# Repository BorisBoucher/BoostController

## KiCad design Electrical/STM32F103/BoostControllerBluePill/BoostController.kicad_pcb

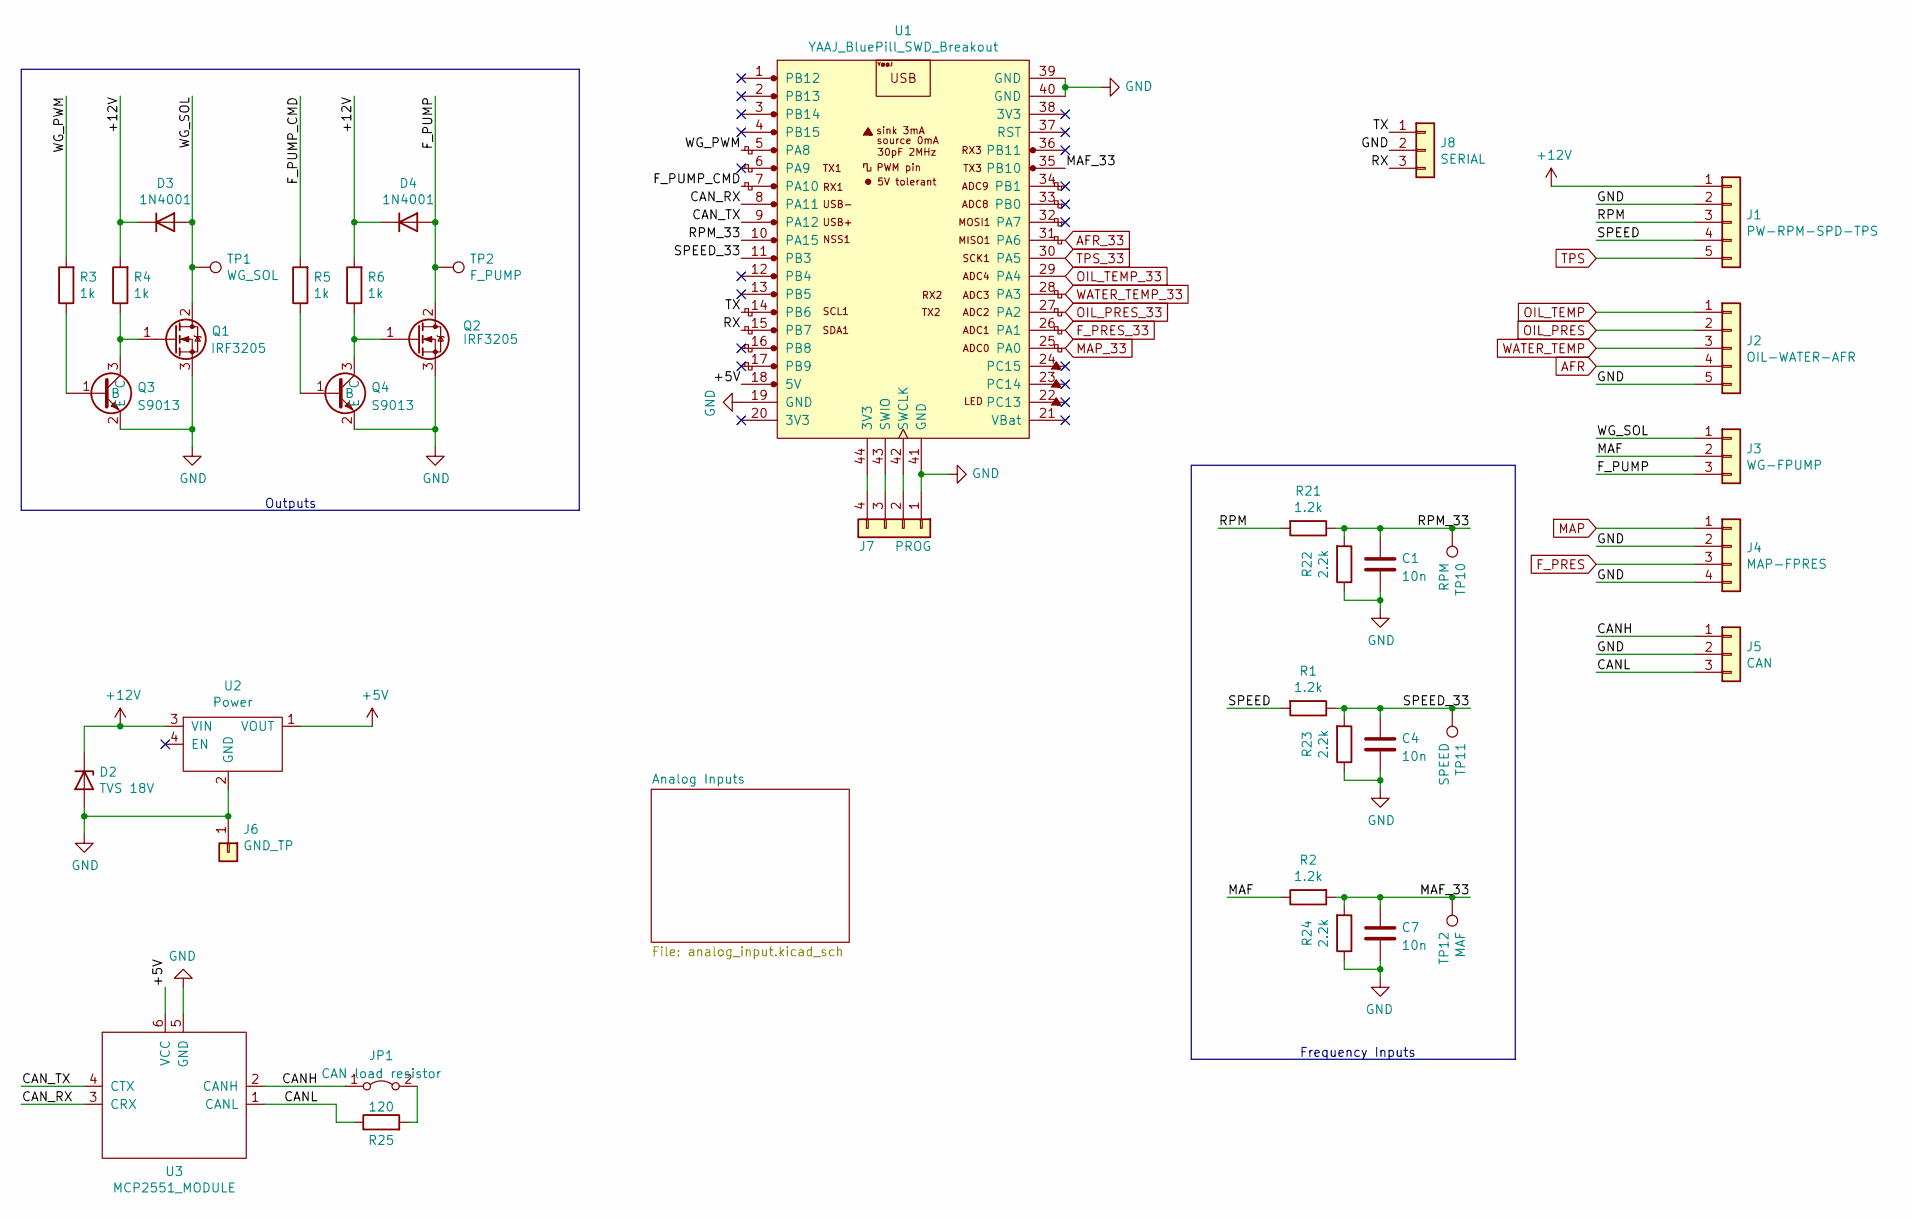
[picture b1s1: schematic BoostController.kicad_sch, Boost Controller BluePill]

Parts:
C1, C4, C7: 10n; C_0603_1608Metric_Pad1.08x0.95mm_HandSolder
D2: TVS 18V; D_DO-41_SOD81_P5.08mm_Vertical_AnodeUp
D3, D4: 1N4001; D_DO-41_SOD81_P2.54mm_Vertical_AnodeUp
J1: PW-RPM-SPD-TPS; JST_XH_S5B-XH-A-1_1x05_P2.50mm_Horizontal
J2: OIL-WATER-AFR; JST_XH_S5B-XH-A-1_1x05_P2.50mm_Horizontal
J3: WG-FPUMP; JST_XH_S3B-XH-A-1_1x03_P2.50mm_Horizontal
J4: MAP-FPRES; JST_XH_S4B-XH-A-1_1x04_P2.50mm_Horizontal
J5: CAN; JST_XH_S3B-XH-A-1_1x03_P2.50mm_Horizontal
J6: GND_TP; Pin_Header_Straight_1x01_Pitch2.54mm
J7: PROG; PinHeader_1x04_P2.54mm_Vertical
J8: SERIAL; PinHeader_1x03_P2.54mm_Vertical
JP1: CAN load resistor; PinHeader_1x02_P2.54mm_Vertical
Q1, Q2: IRF3205; TO-220-3_Vertical
Q3, Q4: S9013; SOT-23
R1, R2, R21: 1.2k; R_1206_3216Metric_Pad1.30x1.75mm_HandSolder
R3, R4, R5, R6: 1k; R_1206_3216Metric_Pad1.30x1.75mm_HandSolder
R22, R23, R24: 2.2k; R_1206_3216Metric_Pad1.30x1.75mm_HandSolder
R25: 120; R_1206_3216Metric_Pad1.30x1.75mm_HandSolder
TP1: WG_SOL; Measurement_Point_Round-SMD-Pad_Big
TP2: F_PUMP; Measurement_Point_Round-SMD-Pad_Big
TP10: RPM; TestPoint_Pad_D3.0mm
TP11: SPEED; TestPoint_Pad_D3.0mm
TP12: MAF; TestPoint_Pad_D3.0mm
U1: YAAJ_BluePill_SWD_Breakout; YAAJ_BluePill_SWD_1
U2: Power; MICRO-BUCK-POWER-MODULE_FLAT
U3: MCP2551_MODULE

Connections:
+5V: U1.18 (5V), U2.1 (VOUT), U3.6 (VCC); also elsewhere on the board
+12V: D2.1 (K), D3.1 (K), D4.1 (K), J1.1, R4.2, R6.2, U2.3 (VIN)
/CANH: J5.1, JP1.1 (A), U3.2 (CANH)
/CANL: J5.3, R25.1, U3.1 (CANL)
/CAN_RX: U1.8 (PA11), U3.3 (CRX)
/CAN_TX: U1.9 (PA12), U3.4 (CTX)
/F_PUMP: D4.2 (A), J3.3, Q2.2 (D), TP2.1
/F_PUMP_CMD: R5.2, U1.7 (PA10)
/MAF: J3.2, R2.1
/MAF_33: C7.1, R2.2, R24.2, TP12.1, U1.35 (PB10)
/RPM: J1.3, R21.2
/RPM_33: C1.1, R21.1, R22.2, TP10.1, U1.10 (PA15)
/RX: J8.3, U1.15 (PB7)
/SPEED: J1.4, R1.2
/SPEED_33: C4.1, R1.1, R23.2, TP11.1, U1.11 (PB3)
/TX: J8.1, U1.14 (PB6)
/WG_PWM: R3.2, U1.5 (PA8)
/WG_SOL: D3.2 (A), J3.1, Q1.2 (D), TP1.1
AFR: J2.4; also elsewhere on the board
AFR_33: U1.31 (PA6); also elsewhere on the board
F_PRES: J4.3; also elsewhere on the board
F_PRES_33: U1.26 (PA1); also elsewhere on the board
GND: C1.2, C4.2, C7.2, D2.2 (A), J1.2, J2.5, J4.2, J4.4, J5.2, J6.1, J7.1, J8.2, Q1.3 (S), Q2.3 (S), Q3.2 (E), Q4.2 (E), R22.1, R23.1, R24.1, U1.19 (GND), U1.39 (GND), U1.40 (GND), U1.41 (GND), U2.2 (GND), U3.5 (GND); also elsewhere on the board
MAP: J4.1; also elsewhere on the board
MAP_33: U1.25 (PA0); also elsewhere on the board
unnamed: J7.2, U1.42 (SWCLK)
unnamed: J7.3, U1.43 (SWIO)
unnamed: J7.4, U1.44 (3V3)
unnamed: JP1.2 (B), R25.2
unnamed: Q1.1 (G), Q3.3 (C), R4.1
unnamed: Q2.1 (G), Q4.3 (C), R6.1
unnamed: Q3.1 (B), R3.1
unnamed: Q4.1 (B), R5.1
OIL_PRES: J2.2; also elsewhere on the board
OIL_PRES_33: U1.27 (PA2); also elsewhere on the board
OIL_TEMP: J2.1; also elsewhere on the board
OIL_TEMP_33: U1.29 (PA4); also elsewhere on the board
TPS: J1.5; also elsewhere on the board
TPS_33: U1.30 (PA5); also elsewhere on the board
WATER_TEMP: J2.3; also elsewhere on the board
WATER_TEMP_33: U1.28 (PA3); also elsewhere on the board

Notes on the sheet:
Frequency Inputs
Outputs

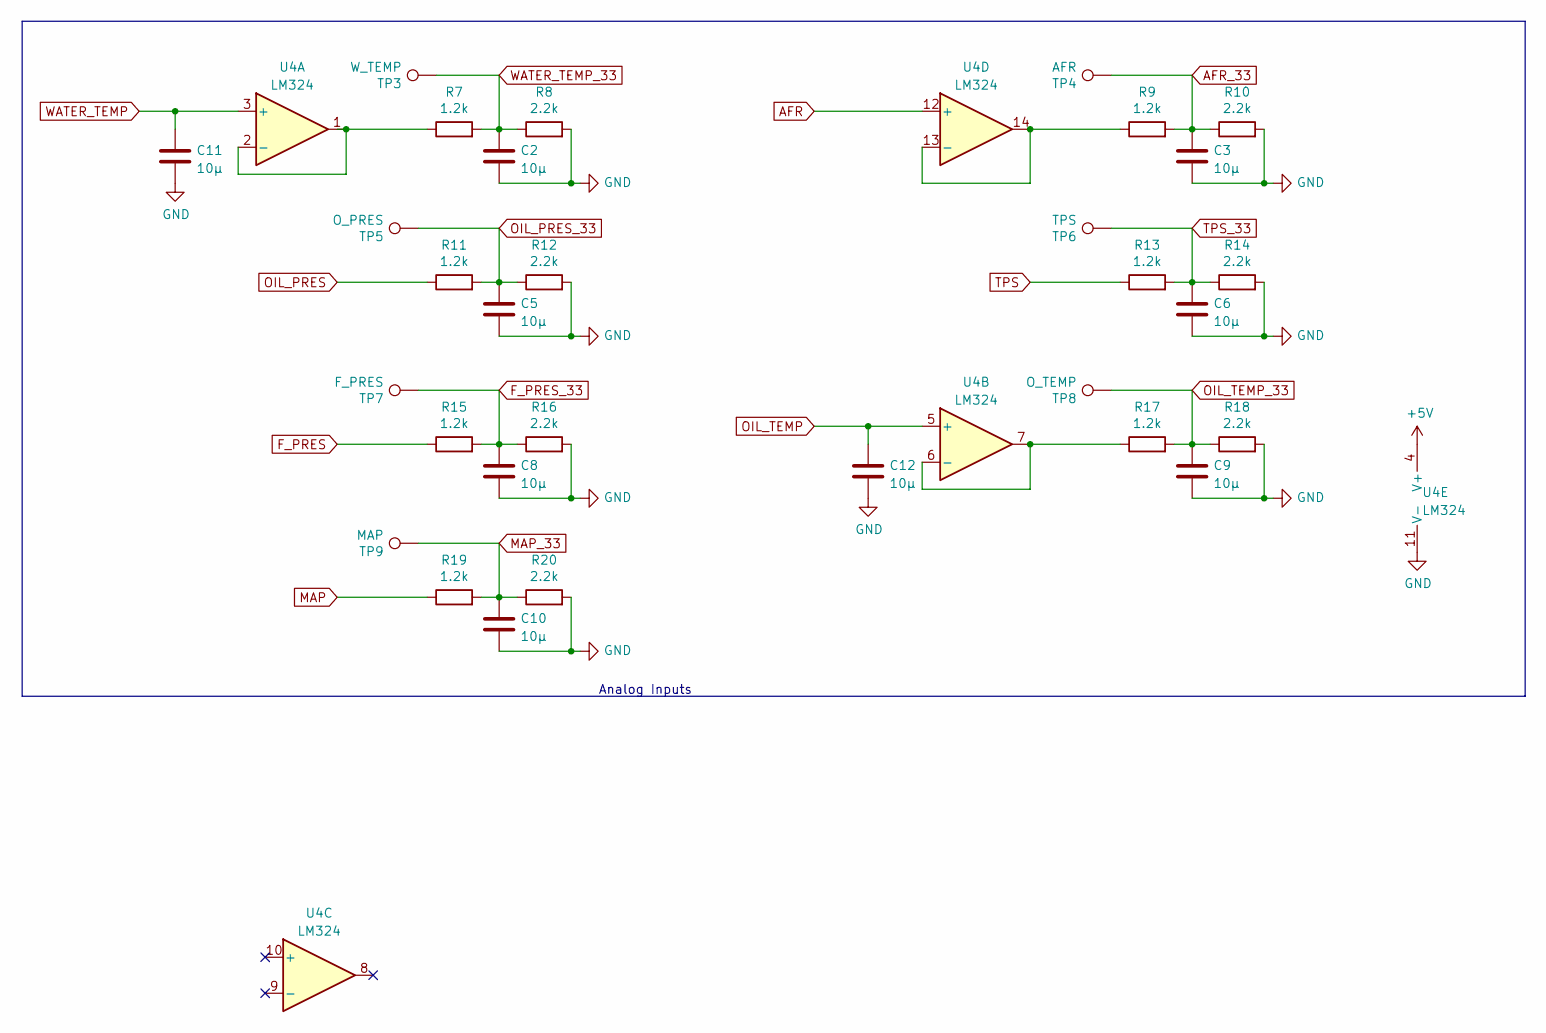
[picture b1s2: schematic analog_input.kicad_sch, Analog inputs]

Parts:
C2, C3, C5, C6, C8, C9, C10, C11, C12: 10µ; C_0603_1608Metric_Pad1.08x0.95mm_HandSolder
R7, R9, R11, R13, R15, R17, R19: 1.2k; R_1206_3216Metric_Pad1.30x1.75mm_HandSolder
R8, R10, R12, R14, R16, R18, R20: 2.2k; R_1206_3216Metric_Pad1.30x1.75mm_HandSolder
TP3: W_TEMP; Measurement_Point_Round-SMD-Pad_Big
TP4: AFR; Measurement_Point_Round-SMD-Pad_Big
TP5: O_PRES; Measurement_Point_Round-SMD-Pad_Big
TP6: TPS; Measurement_Point_Round-SMD-Pad_Big
TP7: F_PRES; Measurement_Point_Round-SMD-Pad_Big
TP8: O_TEMP; Measurement_Point_Round-SMD-Pad_Big
TP9: MAP; Measurement_Point_Round-SMD-Pad_Big
U4: LM324

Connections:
+5V: U4.4 (V+); also elsewhere on the board
AFR: U4.12 (+); also elsewhere on the board
AFR_33: C3.1, R9.2, R10.1, TP4.1; also elsewhere on the board
F_PRES: R15.1; also elsewhere on the board
F_PRES_33: C8.1, R15.2, R16.1, TP7.1; also elsewhere on the board
GND: C2.2, C3.2, C5.2, C6.2, C8.2, C9.2, C10.2, C11.2, C12.2, R8.2, R10.2, R12.2, R14.2, R16.2, R18.2, R20.2, U4.11 (V-); also elsewhere on the board
MAP: R19.1; also elsewhere on the board
MAP_33: C10.1, R19.2, R20.1, TP9.1; also elsewhere on the board
unnamed: R7.1, U4.1, U4.2 (-)
unnamed: R9.1, U4.13 (-), U4.14
unnamed: R17.1, U4.6 (-), U4.7
OIL_PRES: R11.1; also elsewhere on the board
OIL_PRES_33: C5.1, R11.2, R12.1, TP5.1; also elsewhere on the board
OIL_TEMP: C12.1, U4.5 (+); also elsewhere on the board
OIL_TEMP_33: C9.1, R17.2, R18.1, TP8.1; also elsewhere on the board
TPS: R13.1; also elsewhere on the board
TPS_33: C6.1, R13.2, R14.1, TP6.1; also elsewhere on the board
WATER_TEMP: C11.1, U4.3 (+); also elsewhere on the board
WATER_TEMP_33: C2.1, R7.2, R8.1, TP3.1; also elsewhere on the board

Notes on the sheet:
Analog Inputs

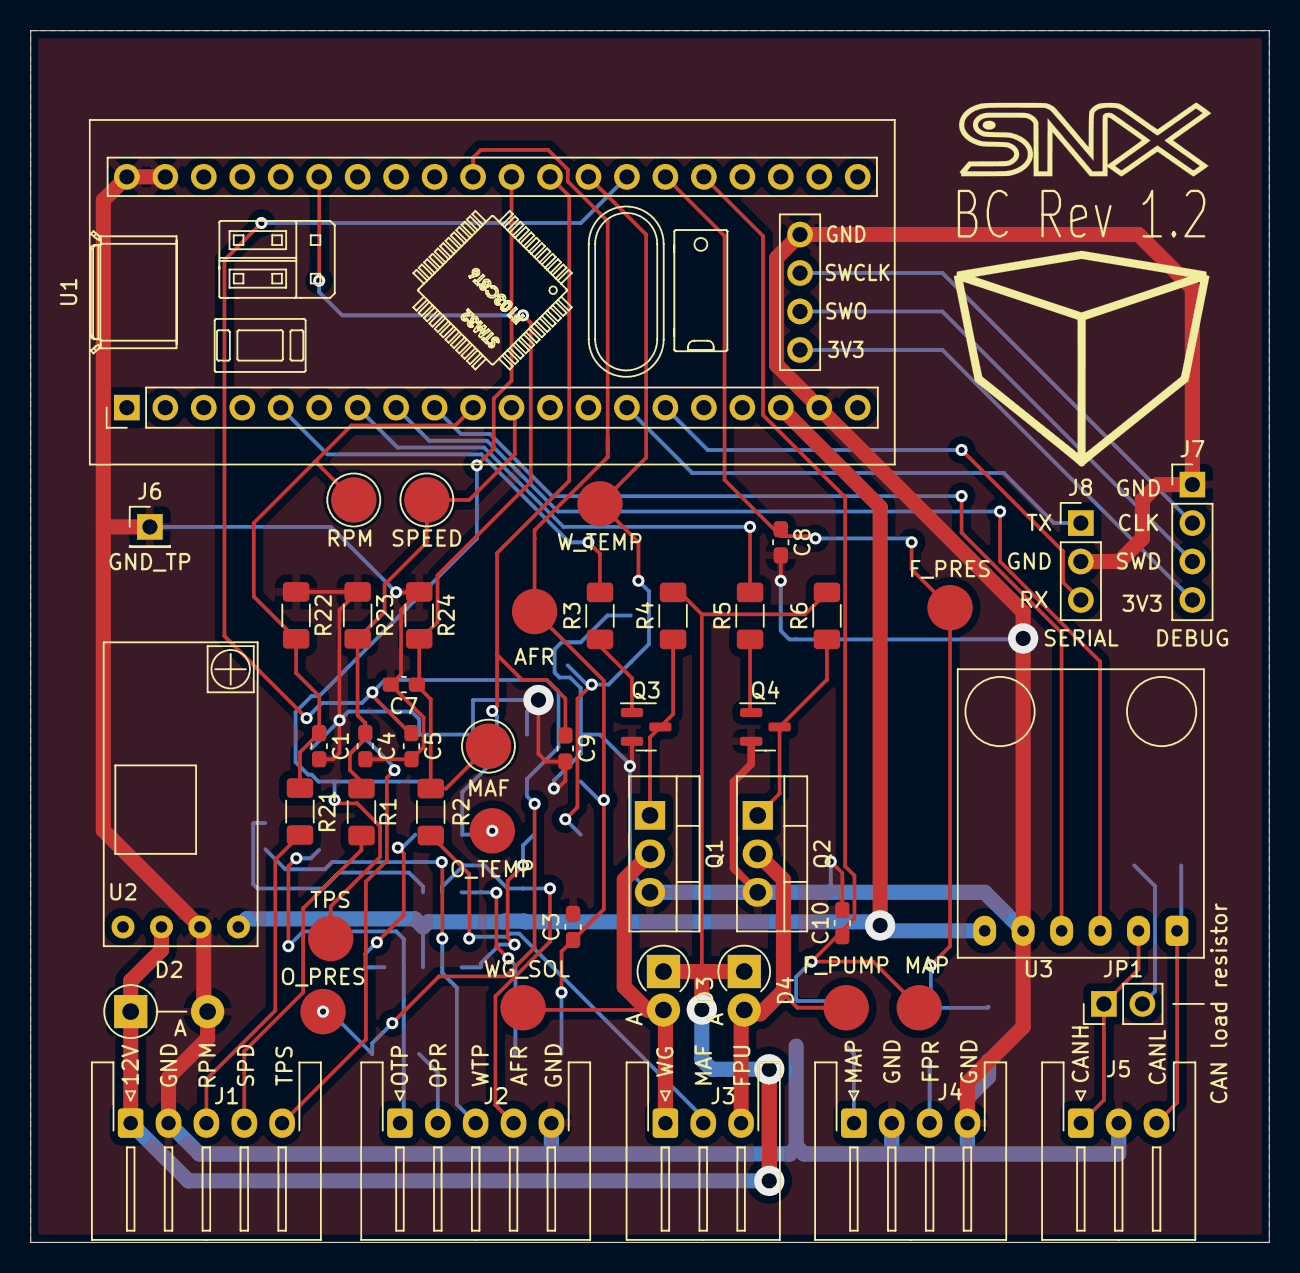
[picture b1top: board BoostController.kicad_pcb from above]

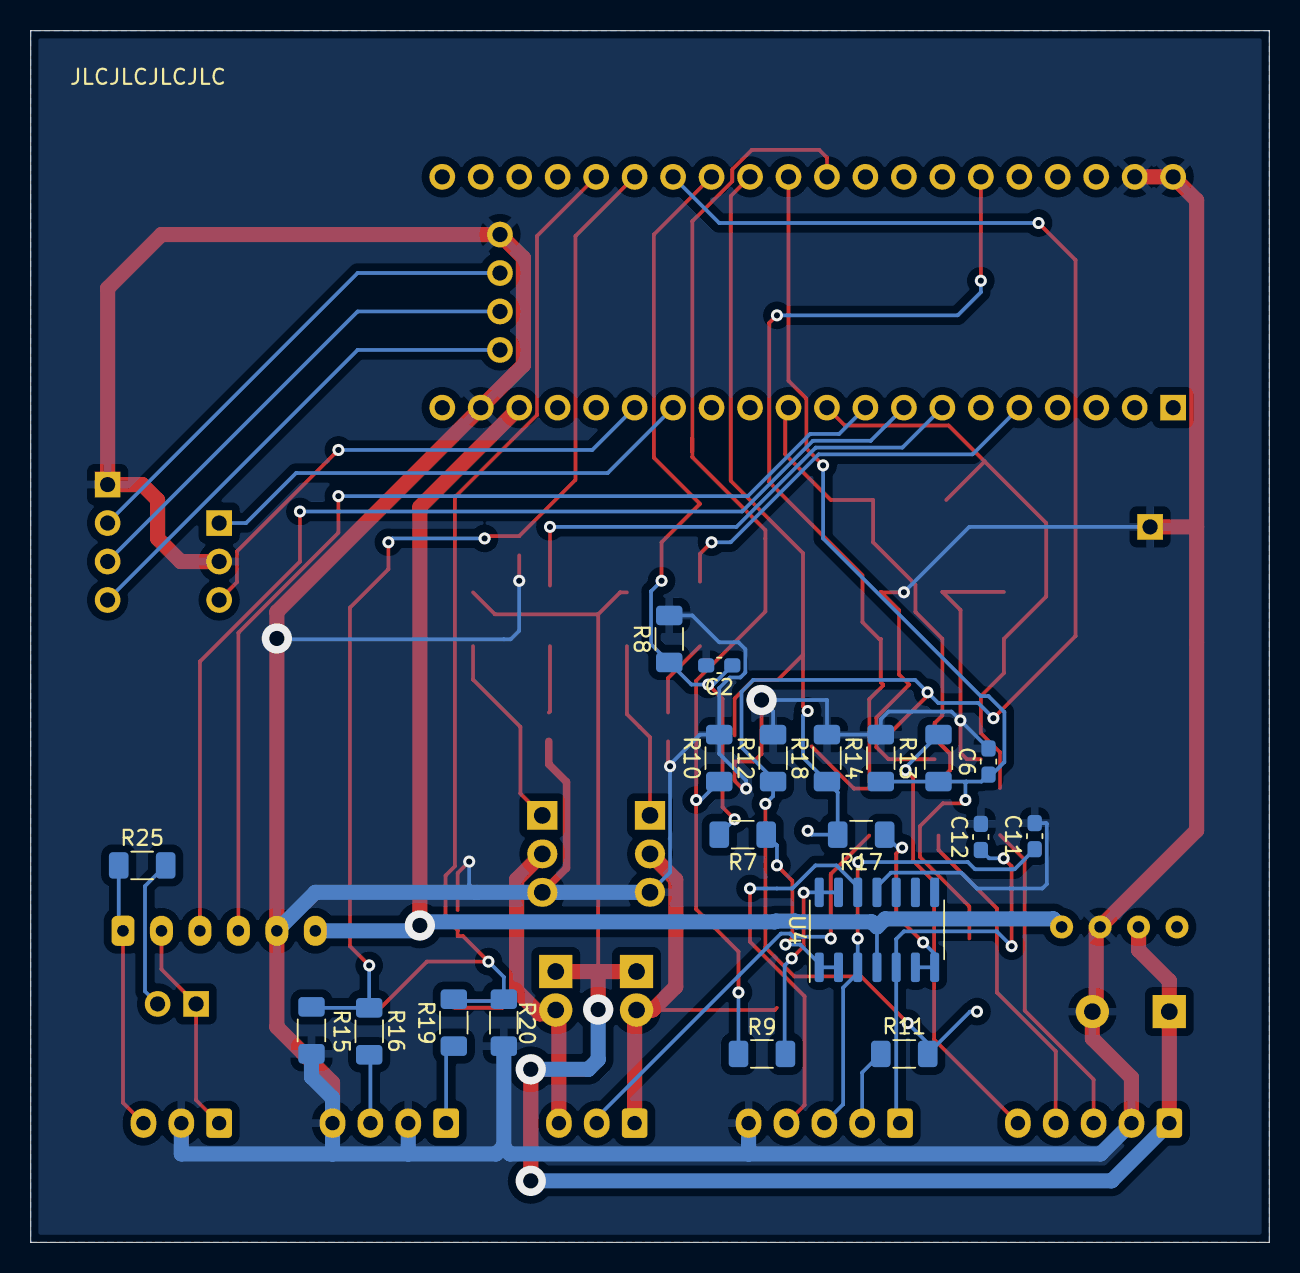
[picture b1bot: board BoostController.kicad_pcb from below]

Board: 2 copper layers, 81.8 x 80.0 mm, 71 parts (20 on the bottom side), 44 nets.

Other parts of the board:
Ref**: Val**; logo_cube
Ref**#2: Val**; SNX_little

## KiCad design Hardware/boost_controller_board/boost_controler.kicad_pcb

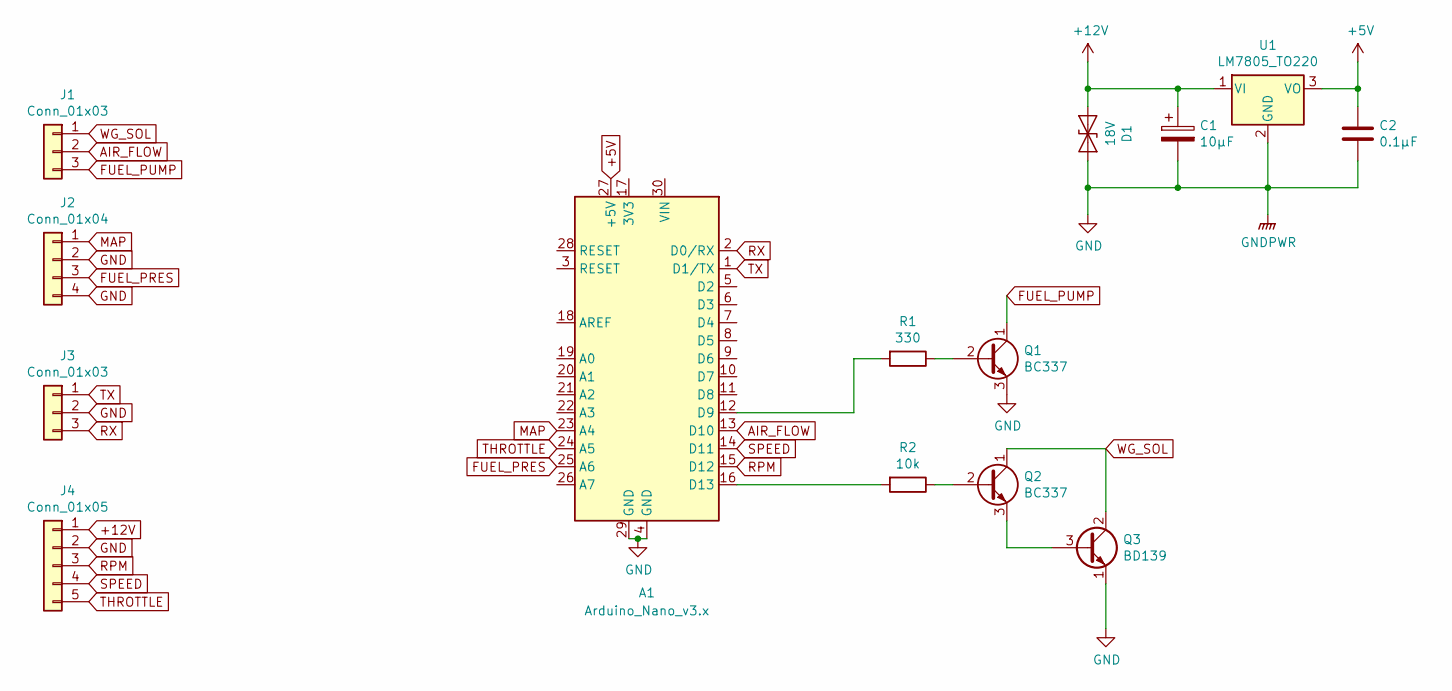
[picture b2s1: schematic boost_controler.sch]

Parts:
A1: Arduino_Nano_v3.x; ARDNANO30NP
C1: 10µF; CP_Radial_D8.0mm_P5.00mm
C2: 0.1µF; C_Disc_D3.0mm_W2.0mm_P2.50mm
D1: 18V; D_5W_P10.16mm_Horizontal
J1, J3: Conn_01x03; JST_XH_3x2.50mm_TH_Angled
J2: Conn_01x04; JST_XH_4x2.50mm_TH_Angled
J4: Conn_01x05; JST_XH_5x2.50mm_TH_Angled
Q1, Q2: BC337; TO-92_Inline_Wide
Q3: BD139; TO-126_Vertical
R1: 330; R_Axial_DIN0204_L3.6mm_D1.6mm_P2.54mm_Vertical
R2: 10k; R_Axial_DIN0204_L3.6mm_D1.6mm_P2.54mm_Vertical
U1: LM7805_TO220; TO-220-3_Vertical

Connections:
+5V: A1.27 (+5V), C2.1, U1.3 (VO)
+12V: C1.1, D1.1 (A1), J4.1, U1.1 (VI)
AIR_FLOW: A1.13 (D10), J1.2
FUEL_PRES: A1.25 (A6), J2.3
FUEL_PUMP: J1.3, Q1.1 (C)
GND: A1.4 (GND), A1.29 (GND), C1.2, C2.2, D1.2 (A2), J2.2, J2.4, J3.2, J4.2, Q1.3 (E), Q3.1 (E), U1.2 (GND)
MAP: A1.23 (A4), J2.1
unnamed: A1.12 (D9), R1.2
unnamed: A1.16 (D13), R2.2
unnamed: Q1.2 (B), R1.1
unnamed: Q2.2 (B), R2.1
unnamed: Q2.3 (E), Q3.3 (B)
RPM: A1.15 (D12), J4.3
RX: A1.2 (D0/RX), J3.3
SPEED: A1.14 (D11), J4.4
THROTTLE: A1.24 (A5), J4.5
TX: A1.1 (D1/TX), J3.1
WG_SOL: J1.1, Q2.1 (C), Q3.2 (C)

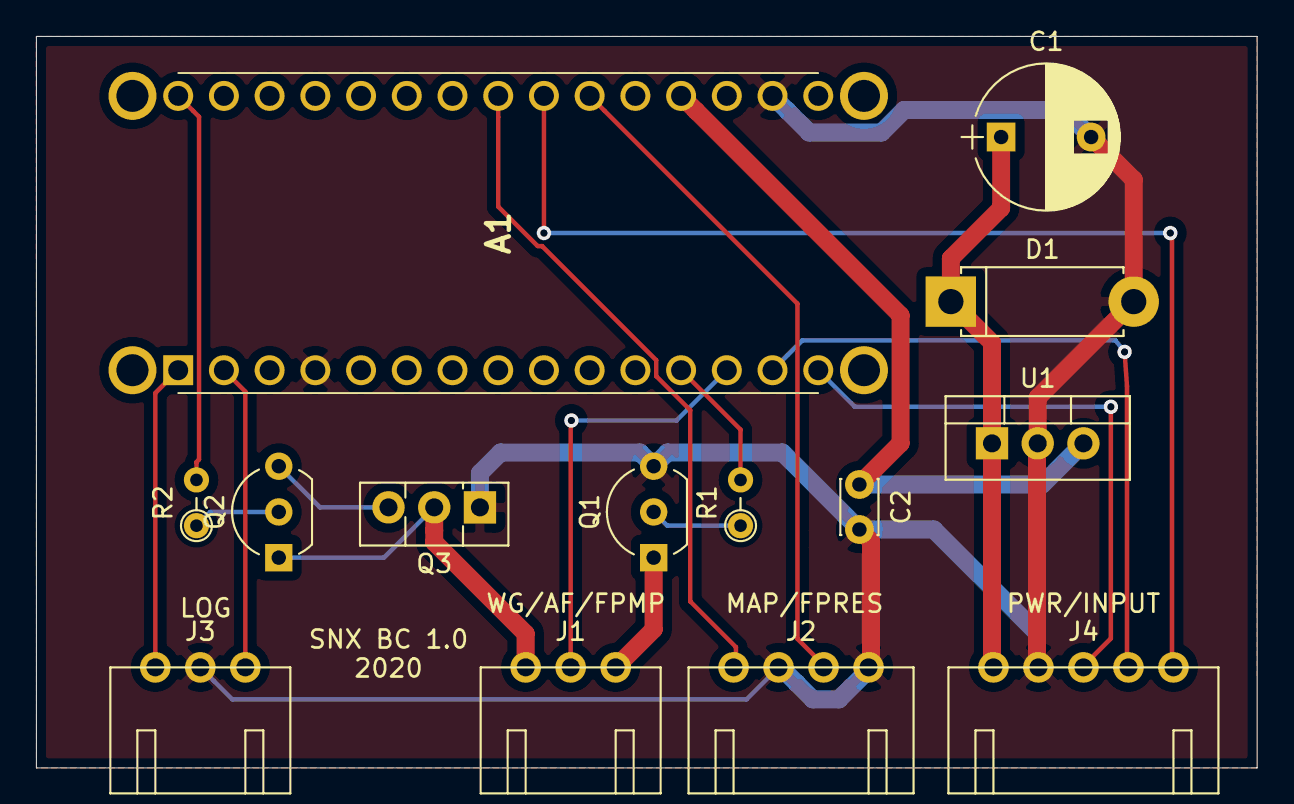
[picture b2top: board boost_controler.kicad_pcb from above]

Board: 2 copper layers, 67.8 x 40.6 mm, 14 parts (0 on the bottom side), 18 nets.

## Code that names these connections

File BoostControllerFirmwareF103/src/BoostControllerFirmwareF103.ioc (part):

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Mcu.Name=STM32F103C(8-B)Tx
Mcu.Package=LQFP48
Mcu.UserName=STM32F103C8Tx
PA0-WKUP.GPIOParameters=GPIO_Label
PA0-WKUP.GPIO_Label=MAP
PA0-WKUP.Signal=ADCx_IN0
PA1.GPIOParameters=GPIO_Label
PA1.GPIO_Label=FUEL_PRES
PA1.Signal=ADCx_IN1
PA10.GPIOParameters=GPIO_Label
PA10.GPIO_Label=FUEL_P
PA10.Signal=GPIO_Output
PA11.Mode=CAN_Activate
PA11.Signal=CAN_RX
PA12.Mode=CAN_Activate
PA12.Signal=CAN_TX
PA13.Mode=Serial_Wire
PA13.Signal=SYS_JTMS-SWDIO
PA14.Mode=Serial_Wire
PA14.Signal=SYS_JTCK-SWCLK
PA15.GPIOParameters=GPIO_Label
PA15.GPIO_Label=RPM_HZ
PA15.Signal=S_TIM2_CH1_ETR
PA2.GPIOParameters=GPIO_Label
PA2.GPIO_Label=OIL_PRES
PA2.Signal=ADCx_IN2
PA3.GPIOParameters=GPIO_Label
PA3.GPIO_Label=WATER_TEMP
PA3.Signal=ADCx_IN3
PA4.GPIOParameters=GPIO_Label
PA4.GPIO_Label=OIL_TEMP
PA4.Signal=ADCx_IN4
PA5.GPIOParameters=GPIO_Label
PA5.GPIO_Label=TPS
PA5.Signal=ADCx_IN5
PA6.GPIOParameters=GPIO_Label
PA6.GPIO_Label=AFR
PA6.Signal=ADCx_IN6
PA8.GPIOParameters=GPIO_Label
PA8.GPIO_Label=WG_PWM
PA8.Signal=S_TIM1_CH1
PB10.GPIOParameters=GPIO_Label
PB10.GPIO_Label=MAF_HZ
PB10.Signal=S_TIM2_CH3
PB3.GPIOParameters=GPIO_Label
PB3.GPIO_Label=SPEED_HZ
PB3.Signal=S_TIM2_CH2
PB6.Mode=Asynchronous
PB6.Signal=USART1_TX
PB7.Mode=Asynchronous
PB7.Signal=USART1_RX
PC14-OSC32_IN.Mode=LSE-External-Oscillator
PC14-OSC32_IN.Signal=RCC_OSC32_IN
PC15-OSC32_OUT.Mode=LSE-External-Oscillator
PC15-OSC32_OUT.Signal=RCC_OSC32_OUT
PD0-OSC_IN.Mode=HSE-External-Oscillator
PD0-OSC_IN.Signal=RCC_OSC_IN
PD1-OSC_OUT.Mode=HSE-External-Oscillator
PD1-OSC_OUT.Signal=RCC_OSC_OUT
RCC.SYSCLKFreq_VALUE=72000000
RCC.SYSCLKSource=RCC_SYSCLKSOURCE_PLLCLK
board=custom

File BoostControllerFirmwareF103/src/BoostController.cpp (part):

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  
	SPI for CAN MCP2515:
		#CS		PIN 10, Port PB2
		MOSI	PIN 11, Port PB3
		MISO	PIN 12, Port PB4
		SCK		PIN 13, Port PB5
		INT		PIN 3,  Port PD3 (INT1)

	Engine/car input:
		RPM				: PIN 7, port PD7
		SPEED			: PIN 6, port PD6
		MAF				: PIN 5, port PD5
		Throttle input	: PIN A7, ADC7, port AC7
		MAP input		: PIN A6, ADC6, port AC6
	
	Output:
		Solenoid output : PIN 4, port PD4
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	switch (output)
	{
	case SOLENOID_OUT:
		HAL_GPIO_WritePin(WG_PWM_GPIO_Port, WG_PWM_Pin, state ? GPIO_PIN_SET : GPIO_PIN_RESET);
		break;
	case FUEL_PUMP_OUT:
		HAL_GPIO_WritePin(FUEL_P_GPIO_Port, FUEL_P_Pin, state ? GPIO_PIN_SET : GPIO_PIN_RESET);
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	// We don't have MAF or VE info, so the load is a simple approximation based on MAP :
	// 	0 bar MAP => 0% load,
	//	2 bar MAP => 100% load (2 bar MAP means 1 bar turbo pressure)
	mMeasures.LOAD = constrain((mMeasures.MAP * 0.5f) * 100.0f, 0.0f, 100.0f);
	gParamIndex.setParam(ParamID::LOAD, mMeasures.LOAD, false);

//! 7ms
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//! 10ms

	// Convert target output to solenoid DC
	// We need a conversion constant to map a boost value to a solenoid DC
	// target output is in absolute pressure, convert it to relative pressure.
	// DC is updated only once per sol cycle
	float relativeTarget = mMeasures.TARGET_OUTPUT; // - 1.0f;
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void HAL_CAN_RxFifo0MsgPendingCallback(CAN_HandleTypeDef *hcan)
{
	my_HAL_CAN_RxFifo0MsgPendingCallback(hcan);
	// const auto& map = CANCommProvider::getMap();
	// auto it = map.find(hcan);
	// if (it != map.end())
	// {
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
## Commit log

2018-10-09 Backup before SnxProtocol
2019-12-08 Added simulation variable for testing
2019-12-31 Added speed and RPM on graph 2 Added toolbar with shortcuts to activates logs, BC comm & MUT comm Added test function to force BS seloneid duty cycle Added MUT protocol reader Added file logger outpu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
2019-12-31 Fixed some file not needed in repo
2020-01-03 BC firmware : Added support for air flow measurment into BC. Changed default boost table. Added debug output during init to track infinite loop. Added debug output pin for testing RMP and Speed acqui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
2020-01-03 Added Arduino firmware for boost controler stimulator. Simulate RMP, Speed and air flow.
2020-01-03 Added schematics for BC proto
2020-01-03 Added snxcomm QT library. Implements the SNX protocol to communicated with BC firmware over serial port.
2020-01-03 Descriptive documents
2020-01-03 VSCode files
2020-01-03 GUI mockup
2020-01-03 Git ignre file
2020-01-05 Correction definition protocol FAST Converted arduino project to VisualStudio Code/platform IO project Added support for FAST protocol in BC firmware Preliminary FAST protocol for QT.
2020-01-18 Fast com protocol implemented. * Added remarks in protocol spec about FTDI serial port RX timeouts. * Added BC emulator for testing fast com implementation in BC configurator. * Implemented fast com 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
2020-01-18 Fast com implemetation * Cleanup project/removed obsolete QT serialport includes/libs * Update data model with new addressing and added missing data. * Added air flow in logger output * Fixed logid i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
2020-01-20 Specific port used for stimulator arduino
2020-01-20 Fixed crash in MUT reader
2020-02-22 Added support for MAF frequency measure Added fiter on MAF frequency Changed documentation of communication address table. Changed to configuration V1. Added code to load old configuration version. R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
2020-03-08 Changed MAF HZ lowpass filter from 50 to 5Hz. Activated pullup on MAF input. Fixed MAF Hz computation (bad time computation). Added thottle correction access to logger. Fixed stimulator MAF frequency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
2020-03-08 Added WG curout at low speed
2020-03-14 Added setting load/save Added log dir configuration Added max throttle configuration
2020-04-12 Added support for fuel pressuse
2020-04-12 Added support for fuel pressure sensor
2020-05-16 Added fuel pump prime on power up Added filtering on throttle pos Fixed fuel pressure scaling Fixed word param table addresses Fixed word write conversion from serial comm
2020-05-16 Added 12V booster management for stimulation board
2020-05-16 Adde voltage booster
2020-05-16 Added fuel pump prime configuration Added fuel pressure monitoring
2020-05-16 Fixed filter type for measured boost derivative
2020-05-17 Versionning verson 1.0
2020-08-13 Fixed frequency output error on stimulator.
2020-08-13 Added lowpass filter on MAP measure to reduce noise.
2020-08-13 Added stimulator schematic
2020-08-14 Added inno setup installer script and preparation batch file. Changed main window title.
2020-08-23 Definition for MCP2515 CAN ship/WIP
2020-08-23 Doc fixup
2020-08-23 Removed unused files Update fritzing proto design board
2020-08-23 Renamef files and folders
2020-08-23 Minor fix/WIP
2020-08-23 Renamed files and folders
2020-08-24 Fixed typo in controller.
2020-08-24 Cleaned up gitignore. Fixed snxcomm library import in boost configurator project to support debug and release build. Fixed make installer script to support debug and release build.
2020-08-25 Renamed hardware directory
2020-08-25 Added hardware data : Kicad schematic and board proto design, 3D models, fritzing proto for stimulator board.
2020-08-25 Updated git ignore
2021-11-14 Added kicad PCB files rev 1.1
2021-11-14 Porting to BC firmware to STM32f103 BluePill, WIP
2021-11-27 PCB rev 1.1 Fixed track width for solenoid and relay driver Removed spurious hole Cleared overwrites in fab layer Fixed missing name on WG_SOL TP
2022-04-20 PCB rev 1.2 Fixed missing RPM input Ported to Kicad 6 Fixed DRC warning on silkscreen
2022-04-20 Backup fab files
2022-04-25 Fixed SOT-23 transistors. Added test points. Changed footprint to Kicad6.
2022-04-25 Fixed D12 footprint
2022-05-02 Replaced Zener protectio diode (that did not work as expected) with capacitor filter. Replaced MOSFET reference. Clarification on schematic. Changed analog voltage divider resistor values. Added miss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
2022-05-07 Enhanced stimulator air flow output.
2022-05-07 Added support for input capture and ADC. Split source code into config, analog input and input capture support. Fixed ADC conversion configuration. Fixed input capture timing configuration.
2022-05-07 [Electrical] Changed frequency input voltage divider + filter rather than zener diode clamping.
2022-05-15 Added serial port support on dupond header for local data logging. Added missing MAF input resistor. Changed power transistor reference. Changed analog input voltage divisor values.
2022-05-15 [Electrical] Minor fixe
2022-09-14 Added CAN load resistor and jumper
2022-09-18 Added serial comm (in addition to CAN). Added waste gate solenoid PWM control. Fixed ADC conversion table. Converted code to new ADC API. Added configuration default configuration init. Manager for a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
2022-10-29 Fixed stimulator RPM and speed generator
2022-10-29 Arduino version minor update
2022-10-29 Added CAN communication Fixed analog input: workaround 'lost' interrupt. Fixed microsec timer read. Fixed input capture. Added support for reading/writing conf in flash storage. Added support for fue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
2022-11-12 Changed ADC speed to lowest possible to prevent unexplained DMA shifting. Added coolant temp and lambda value in analog measure table
2022-11-12 Enhanced serial bridge code.
2023-02-05 Added OP Amp on analog inputs Split schematics with sub schematic for analog inputs.
2023-02-05 Fixed serial comm. Activated DMA for serial comm. Switched to 230400bps on serial line. Added storage of throttle max conf.
